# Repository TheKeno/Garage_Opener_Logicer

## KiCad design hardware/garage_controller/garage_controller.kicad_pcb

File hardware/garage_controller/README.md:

# Garage controller board (rev A)

A barebones board for `Garage_Opener_Logicer_R6`: an ATmega328P on a 16 MHz
crystal, powered from USB-C, with connectors for everything in the garage. The
chip is pinned out exactly like an Uno, so the sketch runs unchanged.

Open `garage_controller.kicad_pro` in KiCad 10. The schematic passes ERC with
no errors or warnings. The PCB has its outline, all footprints placed and every
pad on its net, and it matches the schematic exactly (DRC with schematic
parity). **It is not routed yet**: the only DRC items left are the 141
unrouted connections.

| File | |
|---|---|
| `garage_controller.kicad_sch` | schematic (A3, one sheet): each block drawn with wires, net labels only between blocks |
| `garage_controller.kicad_pcb` | 120 × 90 mm, 2 layers, placed, unrouted |
| `garage_controller.pdf`, `bom.csv`, `placement.png` | snapshots for reading without KiCad; re-export after edits |

## Connectors

| | Connector | Pins | Notes |
|---|---|---|---|
| J1 | USB-C (power only) | | 5.1k CC pull-downs, so any USB-C charger gives 5 V; 0.75 A polyfuse |
| J4 | LCD, JST-XH 4 | GND, 5V, SDA, SCL | standard PCF8574 backpack order; 4.7k pull-ups on board |
| J5 | Encoder, JST-XH 5 | CLK, DT, SW, +, GND | KY-040 order; SW is wired to D2 with the GUI button, so the knob's push works too |
| J6 | GUI button, JST-XH 2 | BTN, GND | to ground, D2 |
| J7 | Sonar, JST-XH 4 | VCC, TRIG, ECHO, GND | HC-SR04 order; series resistors for the long cable |
| J8 | Door microswitch, JST-XH 2 | SW, GND | 4.7k pull-up plus 1k/100 nF RC against noise on the long run |
| J9 | LDR, JST-XH 2 | 5V, A0 | 10k to ground on board, so more light reads higher |
| J10 | Opener, screw terminal 3 | NC, NO, COM | relay contacts: wire COM (pin 3) and NO (pin 2) across the opener's wall-button terminals |
| J11 | Park assist, JST-XH 5 | 5V, BUZ−, RED, GREEN, GND | 330 Ω on board for the LEDs; an active 5 V buzzer between 5V and BUZ− |
| J12 | ESP8266, 1×7 header | GND, 5V, TX, RX, DOOR_REQ, DOOR_STAT, CAR_STAT | 3.3 V signals; 5 V feeds the ESP board's own regulator |
| J2 | ISP, 2×3 | standard AVR ISP | for burning the bootloader |
| J3 | FTDI, 1×6 | GND, CTS, VCC, TX, RX, DTR | VCC is not connected, so power the board from USB-C while uploading |

## ESP8266 link

The ESP runs at 3.3 V and the ATmega at 5 V, so every line is shifted:

- **ESP TX → ATmega RX:** a BAT85 diode pulls a 10k-pulled-up line low. The idle
  high sits at about 3.6 V, comfortably above the ATmega's 3.0 V threshold.
- **ATmega → ESP** (RX, DOOR_STAT, CAR_STAT): 2.2k/3.3k dividers bring 5 V down
  to 3.0 V.
- **DOOR_REQ:** an NPN transistor plays the push button that R6 expects on D11
  (an active-low input with the internal pull-up). The ESP drives the pin
  **high** to press it. An unplugged ESP reads as "not pressed".

Two things in `esp/dooropener` disagree with R6 and need fixing on the ESP side:

- Its web page shows `DOOR: OPEN` when DOOR_STAT is high, but R6 drives
  `doorStatus` high when the door is **closed**.
- R6's comments describe the ESP as talking over the UART (OPEN / CLOSE /
  STATE …). The ESP sketch in the repo only uses the three pins.

## Building and flashing

1. Fit a **DIP-28 socket**. The footprint is sized for one, but the socket
   isn't in the BOM, so order it separately. Also order JST-XH housings and
   crimps for the cables.
2. Burn the bootloader once over J2. Use a USBasp, or a spare Uno running
   "Arduino as ISP". In the Arduino IDE, pick the **Arduino Uno** board and run
   *Burn Bootloader*. This also sets the fuses for the 16 MHz crystal.
3. Upload R6 over J3 with a 5 V FTDI adapter (DTR resets the chip
   automatically), or keep using the ISP header with *Upload Using Programmer*.
4. **Unplug the ESP for any programming.** It shares the UART with J3, and its
   DOOR_REQ transistor sits on D11, which is MOSI on the ISP header.

## Routing notes

- **Net classes:** a *Power* class (0.8 mm) covers +5V, GND, VBUS and the relay
  nets. Everything else is *Default* (0.3 mm).
- **Ground pour:** a GND zone covers the whole back layer but is left unfilled.
  Press `B` once the tracks are in.
- **Short traces:** keep the crystal (Y1, C6, C7) and the decoupling caps
  (C3, C4) short and close to U1.
- **Relay contacts:** J10's contacts only switch the opener's low-voltage
  button line, so normal clearances are fine. Don't use it for mains.

## Check before ordering

- **USB-C connector:** J1 is the one SMD part. It has six large pads and is
  easy to solder with an iron. Swap it for `Connector:USB_B` with
  `USB_B_OST_USB-B1HSxx_Horizontal` if you'd rather stay fully through-hole.
- **J10 orientation:** check in the 3D viewer that the wire entries face the
  board edge.
- **LDR resistor:** R12 (10k) has to match the resistor in your current build,
  or the light thresholds stored in EEPROM will be off.
- **Power budget:** about 0.6 A peak with the ESP, relay, LCD backlight and
  buzzer all on. Use a charger rated for at least 1 A.

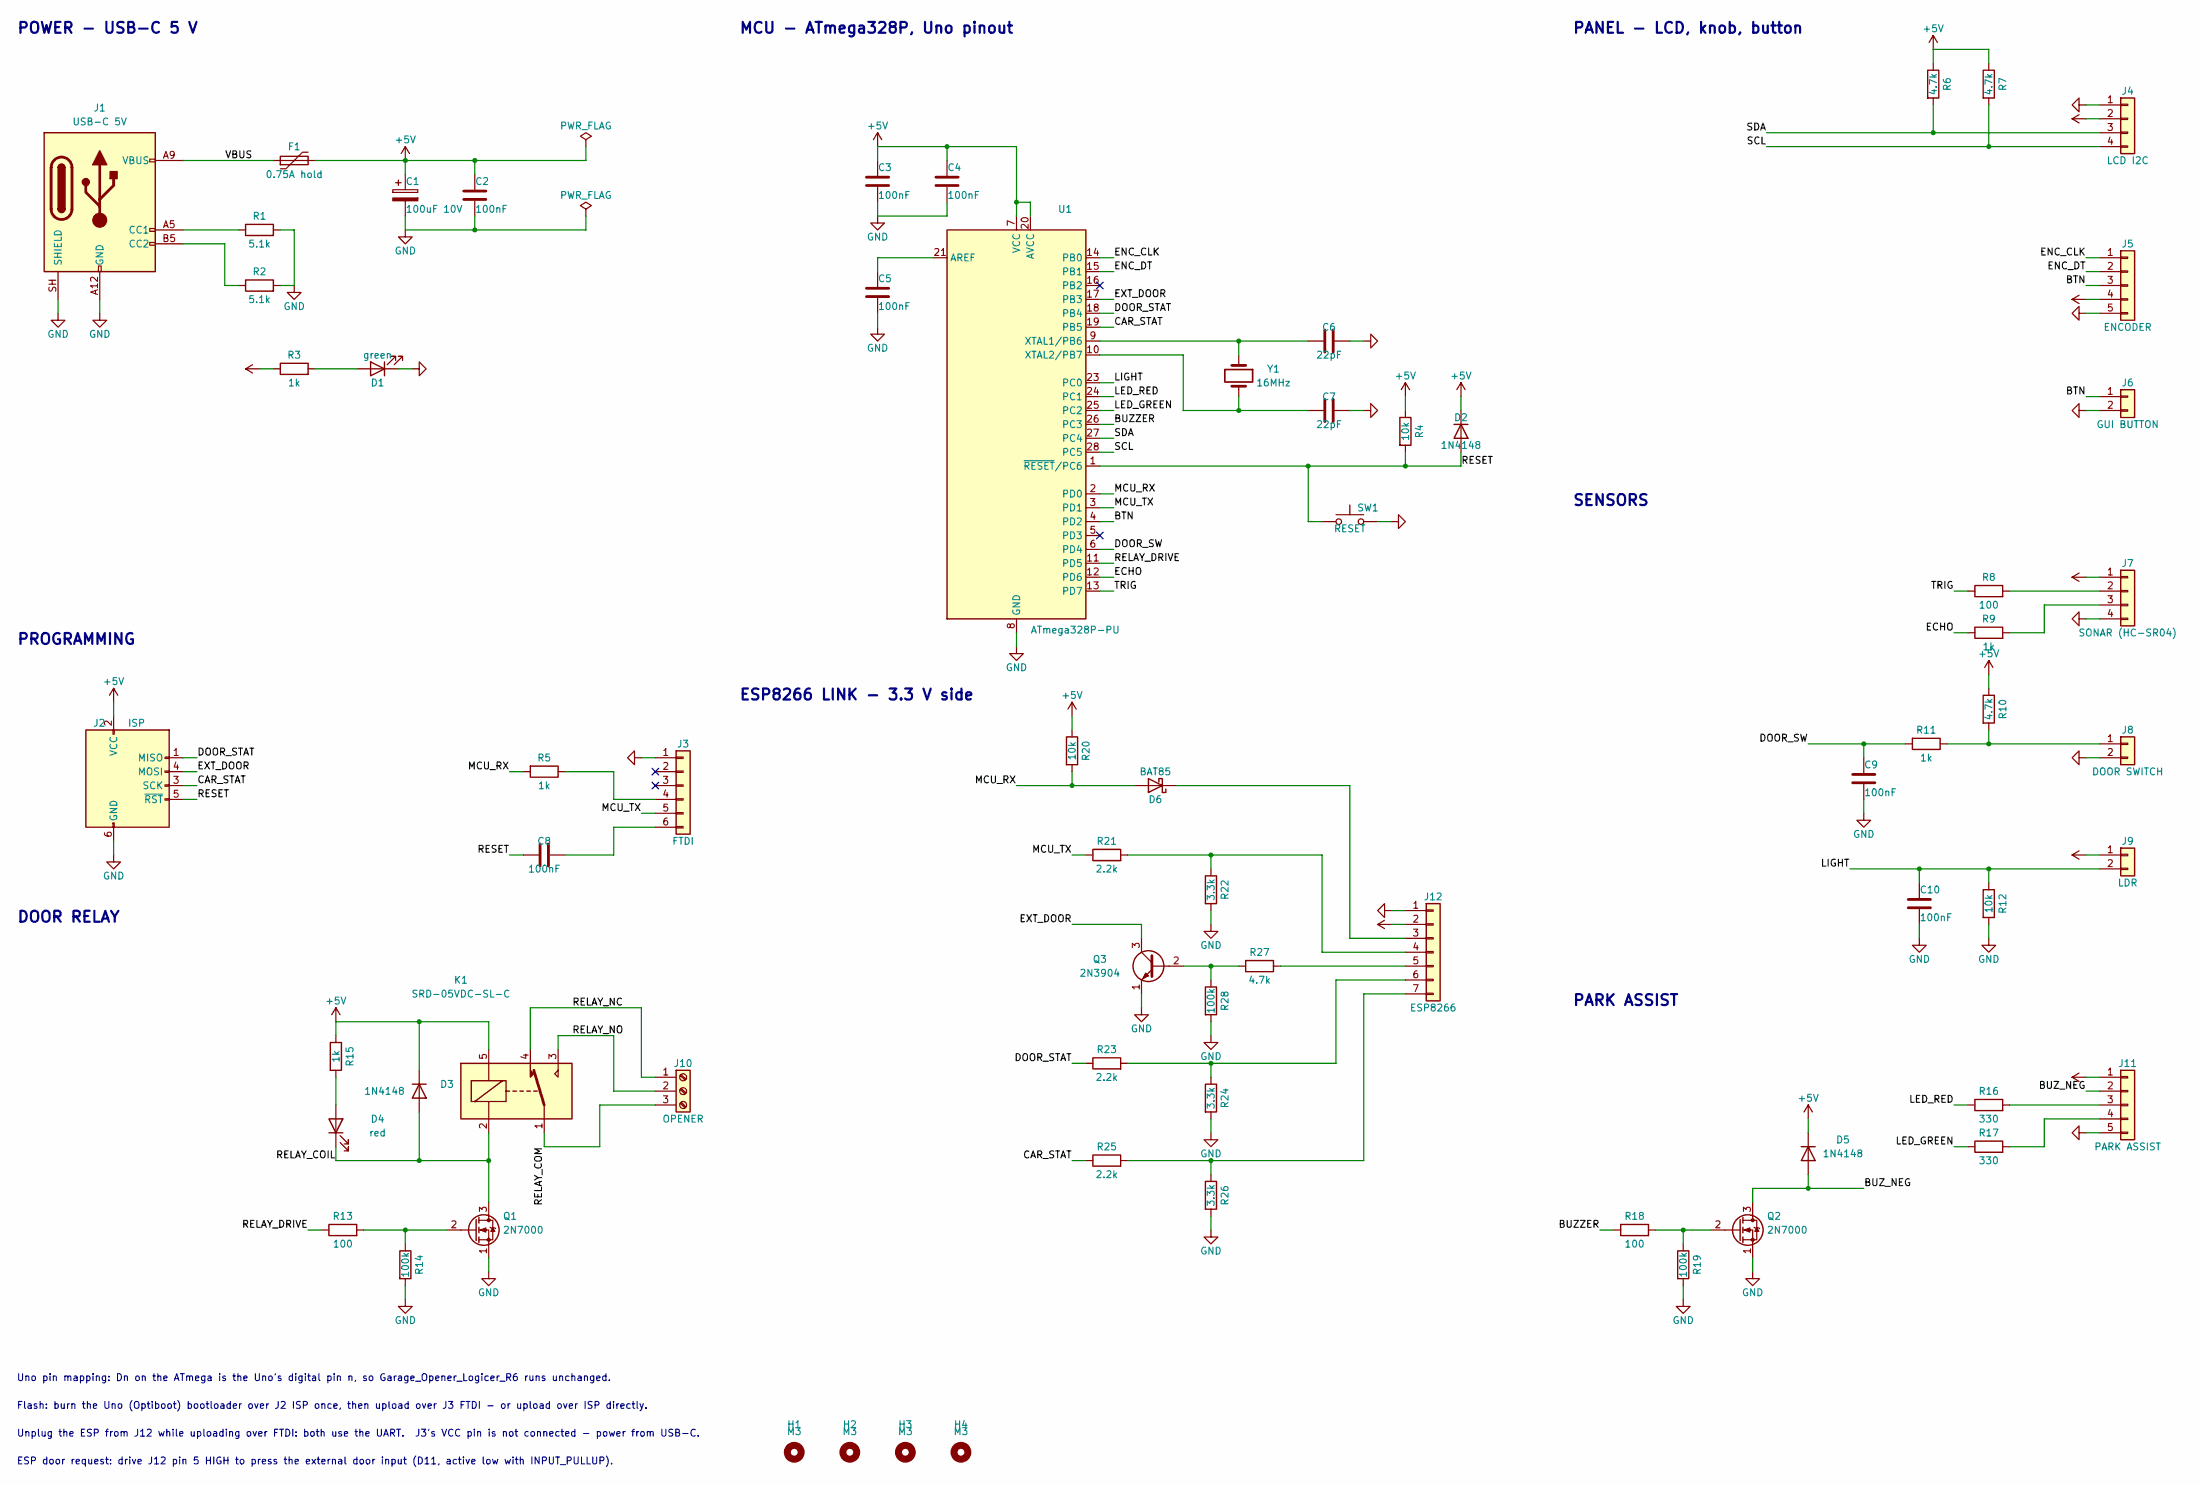
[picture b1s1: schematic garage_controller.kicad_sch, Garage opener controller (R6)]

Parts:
C1: 100uF 10V; CP_Radial_D6.3mm_P2.50mm
C2, C3, C4, C5, C8, C9, C10: 100nF; C_Disc_D5.0mm_W2.5mm_P5.00mm
C6, C7: 22pF; C_Disc_D5.0mm_W2.5mm_P5.00mm
D1: green; LED_D3.0mm
D2, D3, D5: 1N4148; D_DO-35_SOD27_P7.62mm_Horizontal
D4: red; LED_D3.0mm
D6: BAT85; D_DO-35_SOD27_P7.62mm_Horizontal
F1: 0.75A hold; Fuse_BelFuse_0ZRE0075FF_L11.5mm_W4.8mm
H1, H2, H3, H4: M3; MountingHole_3.2mm_M3
J1: USB-C 5V; USB_C_Receptacle_GCT_USB4125-xx-x_6P_TopMnt_Horizontal
J2: ISP; PinHeader_2x03_P2.54mm_Vertical
J3: FTDI; PinHeader_1x06_P2.54mm_Vertical
J4: LCD I2C; JST_XH_B4B-XH-A_1x04_P2.50mm_Vertical
J5: ENCODER; JST_XH_B5B-XH-A_1x05_P2.50mm_Vertical
J6: GUI BUTTON; JST_XH_B2B-XH-A_1x02_P2.50mm_Vertical
J7: SONAR (HC-SR04); JST_XH_B4B-XH-A_1x04_P2.50mm_Vertical
J8: DOOR SWITCH; JST_XH_B2B-XH-A_1x02_P2.50mm_Vertical
J9: LDR; JST_XH_B2B-XH-A_1x02_P2.50mm_Vertical
J10: OPENER; TerminalBlock_Phoenix_MKDS-1,5-3-5.08_1x03_P5.08mm_Horizont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
J11: PARK ASSIST; JST_XH_B5B-XH-A_1x05_P2.50mm_Vertical
J12: ESP8266; PinHeader_1x07_P2.54mm_Vertical
K1: SRD-05VDC-SL-C; Relay_SPDT_SANYOU_SRD_Series_Form_C
Q1, Q2: 2N7000; TO-92_Inline
Q3: 2N3904; TO-92_Inline
R1, R2: 5.1k; R_Axial_DIN0207_L6.3mm_D2.5mm_P10.16mm_Horizontal
R3, R5, R9, R11, R15: 1k; R_Axial_DIN0207_L6.3mm_D2.5mm_P10.16mm_Horizontal
R4, R12, R20: 10k; R_Axial_DIN0207_L6.3mm_D2.5mm_P10.16mm_Horizontal
R6, R7, R10, R27: 4.7k; R_Axial_DIN0207_L6.3mm_D2.5mm_P10.16mm_Horizontal
R8, R13, R18: 100; R_Axial_DIN0207_L6.3mm_D2.5mm_P10.16mm_Horizontal
R14, R19, R28: 100k; R_Axial_DIN0207_L6.3mm_D2.5mm_P10.16mm_Horizontal
R16, R17: 330; R_Axial_DIN0207_L6.3mm_D2.5mm_P10.16mm_Horizontal
R21, R23, R25: 2.2k; R_Axial_DIN0207_L6.3mm_D2.5mm_P10.16mm_Horizontal
R22, R24, R26: 3.3k; R_Axial_DIN0207_L6.3mm_D2.5mm_P10.16mm_Horizontal
SW1: RESET; SW_PUSH_6mm
U1: ATmega328P-PU; DIP-28_W7.62mm_Socket
Y1: 16MHz; Crystal_HC49-4H_Vertical

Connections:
+5V: C1.1, C2.1, C3.1, C4.1, D2.1 (K), D3.1 (K), D5.1 (K), F1.2, J2.2 (VCC), J4.2, J5.4, J7.1, J9.1, J11.1, J12.2, K1.5, R3.1, R4.1, R6.1, R7.1, R10.1, R15.1, R20.1, U1.7 (VCC), U1.20 (AVCC)
/BTN: J5.3, J6.1, U1.4 (PD2)
/BUZZER: R18.1, U1.26 (PC3)
/BUZ_NEG: D5.2 (A), J11.2, Q2.3 (D)
/CAR_STAT: J2.3 (SCK), R25.1, U1.19 (PB5)
/DOOR_STAT: J2.1 (MISO), R23.1, U1.18 (PB4)
/DOOR_SW: C9.1, R11.2, U1.6 (PD4)
/ECHO: R9.1, U1.12 (PD6)
/ENC_CLK: J5.1, U1.14 (PB0)
/ENC_DT: J5.2, U1.15 (PB1)
/EXT_DOOR: J2.4 (MOSI), Q3.3 (C), U1.17 (PB3)
/LED_GREEN: R17.1, U1.25 (PC2)
/LED_RED: R16.1, U1.24 (PC1)
/LIGHT: C10.1, J9.2, R12.1, U1.23 (PC0)
/MCU_RX: D6.2 (A), R5.2, R20.2, U1.2 (PD0)
/MCU_TX: J3.5, R21.1, U1.3 (PD1)
/RELAY_COIL: D3.2 (A), D4.1 (K), K1.2, Q1.3 (D)
/RELAY_COM: J10.3, K1.1
/RELAY_DRIVE: R13.1, U1.11 (PD5)
/RELAY_NC: J10.1, K1.4
/RELAY_NO: J10.2, K1.3
/RESET: C8.2, D2.2 (A), J2.5 (~RST), R4.2, SW1.1, U1.1 (~RESET/PC6)
/SCL: J4.4, R7.2, U1.28 (PC5)
/SDA: J4.3, R6.2, U1.27 (PC4)
/TRIG: R8.1, U1.13 (PD7)
/VBUS: F1.1, J1.A9 (VBUS), J1.B9 (VBUS)
GND: C1.2, C2.2, C3.2, C4.2, C5.2, C6.2, C7.2, C9.2, C10.2, D1.1 (K), J1.A12 (GND), J1.B12 (GND), J1.SH (SHIELD), J2.6 (GND), J3.1, J4.1, J5.5, J6.2, J7.4, J8.2, J11.5, J12.1, Q1.1 (S), Q2.1 (S), Q3.1 (E), R1.2, R2.2, R12.2, R14.2, R19.2, R22.2, R24.2, R26.2, R28.2, SW1.2, U1.8 (GND), U1.22 (GND)
unnamed: D1.2 (A), R3.2
unnamed: D4.2 (A), R15.2
unnamed: D6.1 (K), J12.3
unnamed: J1.A5 (CC1), R1.1
unnamed: J1.B5 (CC2), R2.1
unnamed: J3.4, R5.1
unnamed: C8.1, J3.6
unnamed: J7.2, R8.2
unnamed: J7.3, R9.2
unnamed: J8.1, R10.2, R11.1
unnamed: J11.3, R16.2
unnamed: J11.4, R17.2
unnamed: J12.4, R21.2, R22.1
unnamed: J12.5, R27.1
unnamed: J12.6, R23.2, R24.1
unnamed: J12.7, R25.2, R26.1
unnamed: Q1.2 (G), R13.2, R14.1
unnamed: Q2.2 (G), R18.2, R19.1
unnamed: Q3.2 (B), R27.2, R28.1
unnamed: C5.1, U1.21 (AREF)
unnamed: C6.1, U1.9 (XTAL1/PB6), Y1.1
unnamed: C7.1, U1.10 (XTAL2/PB7), Y1.2

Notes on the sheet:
MCU - ATmega328P, Uno pinout
Unplug the ESP from J12 while uploading over FTDI: both use the UART. J3's VCC pin is not connected - power from USB-C.
Uno pin mapping: Dn on the ATmega is the Uno's digital pin n, so Garage_Opener_Logicer_R6 runs unchanged.
SENSORS
PROGRAMMING
PANEL - LCD, knob, button
Flash: burn the Uno (Optiboot) bootloader over J2 ISP once, then upload over J3 FTDI - or upload over ISP directly.
ESP door request: drive J12 pin 5 HIGH to press the external door input (D11, active low with INPUT_PULLUP).
PARK ASSIST
DOOR RELAY
ESP8266 LINK - 3.3 V side
POWER - USB-C 5 V

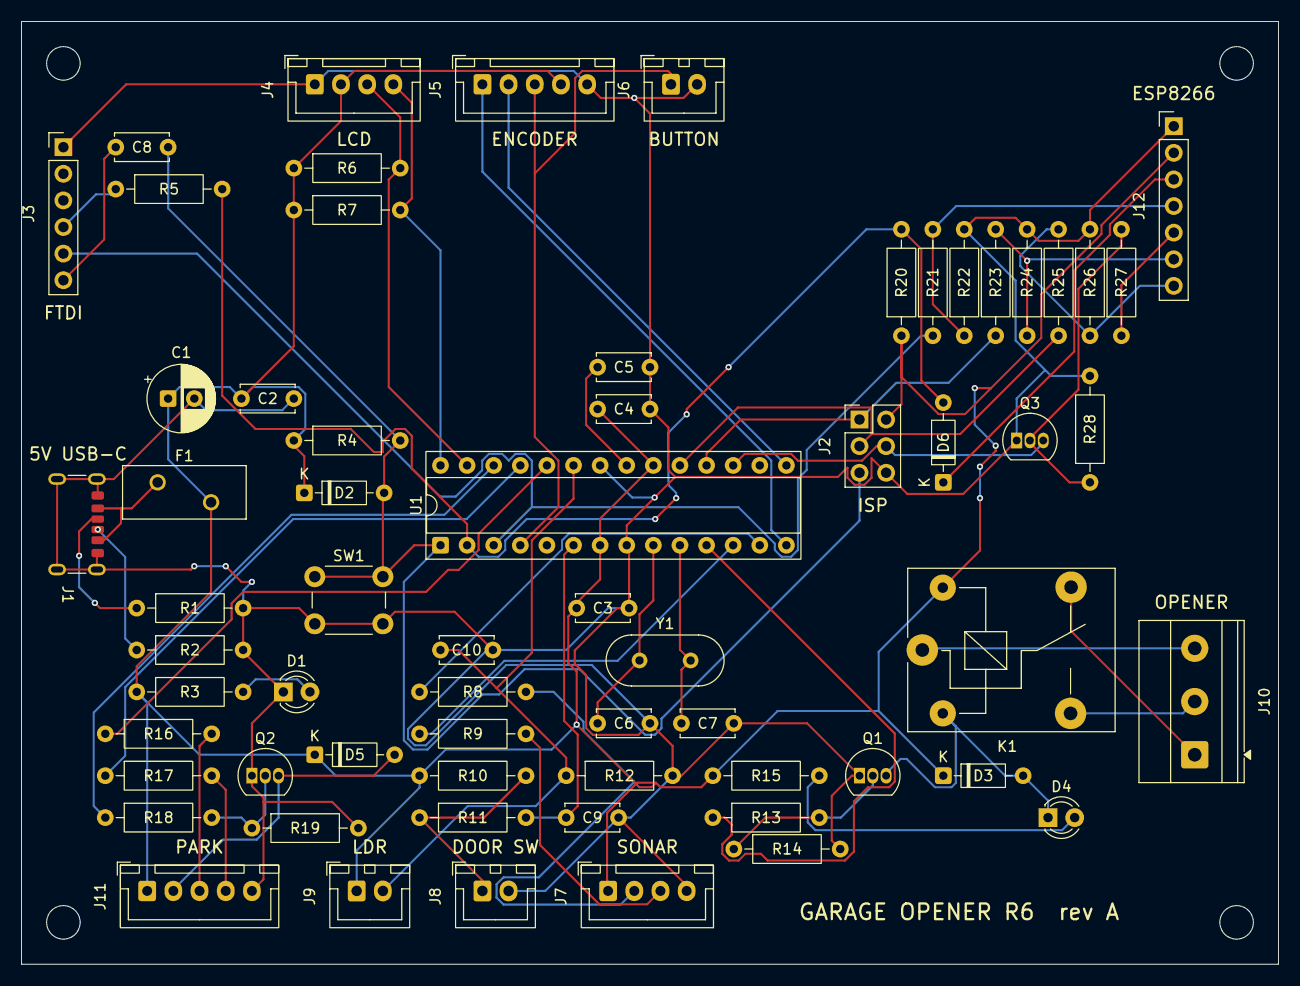
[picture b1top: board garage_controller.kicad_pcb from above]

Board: 2 copper layers, 120.0 x 90.0 mm, 68 parts (0 on the bottom side), 49 nets.

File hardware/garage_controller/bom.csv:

"Refs","Value","Footprint","Qty"
"C1","100uF 10V","Capacitor_THT:CP_Radial_D6.3mm_P2.50mm","1"
"C2,C3,C4,C5,C8,C9,C10","100nF","Capacitor_THT:C_Disc_D5.0mm_W2.5mm_P5.00mm","7"
"C6,C7","22pF","Capacitor_THT:C_Disc_D5.0mm_W2.5mm_P5.00mm","2"
"D1","green","LED_THT:LED_D3.0mm","1"
"D2,D3,D5","1N4148","Diode_THT:D_DO-35_SOD27_P7.62mm_Horizontal","3"
"D4","red","LED_THT:LED_D3.0mm","1"
"D6","BAT85","Diode_THT:D_DO-35_SOD27_P7.62mm_Horizontal","1"
"F1","0.75A hold","Fuse:Fuse_BelFuse_0ZRE0075FF_L11.5mm_W4.8mm","1"
"J1","USB-C 5V","Connector_USB:USB_C_Receptacle_GCT_USB4125-xx-x_6P_TopMnt_Horizontal","1"
"J2","ISP","Connector_PinHeader_2.54mm:PinHeader_2x03_P2.54mm_Vertical","1"
"J3","FTDI","Connector_PinHeader_2.54mm:PinHeader_1x06_P2.54mm_Vertical","1"
"J4","LCD I2C","Connector_JST:JST_XH_B4B-XH-A_1x04_P2.50mm_Vertical","1"
"J5","ENCODER","Connector_JST:JST_XH_B5B-XH-A_1x05_P2.50mm_Vertical","1"
"J6","GUI BUTTON","Connector_JST:JST_XH_B2B-XH-A_1x02_P2.50mm_Vertical","1"
"J7","SONAR (HC-SR04)","Connector_JST:JST_XH_B4B-XH-A_1x04_P2.50mm_Vertical","1"
"J8","DOOR SWITCH","Connector_JST:JST_XH_B2B-XH-A_1x02_P2.50mm_Vertical","1"
"J9","LDR","Connector_JST:JST_XH_B2B-XH-A_1x02_P2.50mm_Vertical","1"
"J10","OPENER","TerminalBlock_Phoenix:TerminalBlock_Phoenix_MKDS-1,5-3-5.08_1x03_P5.08mm_Horizontal","1"
"J11","PARK ASSIST","Connector_JST:JST_XH_B5B-XH-A_1x05_P2.50mm_Vertical","1"
"J12","ESP8266","Connector_PinHeader_2.54mm:PinHeader_1x07_P2.54mm_Vertical","1"
"K1","SRD-05VDC-SL-C","Relay_THT:Relay_SPDT_SANYOU_SRD_Series_Form_C","1"
"Q1,Q2","2N7000","Package_TO_SOT_THT:TO-92_Inline","2"
"Q3","2N3904","Package_TO_SOT_THT:TO-92_Inline","1"
"R1,R2","5.1k","Resistor_THT:R_Axial_DIN0207_L6.3mm_D2.5mm_P10.16mm_Horizontal","2"
"R3,R5,R9,R11,R15","1k","Resistor_THT:R_Axial_DIN0207_L6.3mm_D2.5mm_P10.16mm_Horizontal","5"
"R4,R12,R20","10k","Resistor_THT:R_Axial_DIN0207_L6.3mm_D2.5mm_P10.16mm_Horizontal","3"
"R6,R7,R10,R27","4.7k","Resistor_THT:R_Axial_DIN0207_L6.3mm_D2.5mm_P10.16mm_Horizontal","4"
"R8,R13,R18","100","Resistor_THT:R_Axial_DIN0207_L6.3mm_D2.5mm_P10.16mm_Horizontal","3"
"R14,R19,R28","100k","Resistor_THT:R_Axial_DIN0207_L6.3mm_D2.5mm_P10.16mm_Horizontal","3"
"R16,R17","330","Resistor_THT:R_Axial_DIN0207_L6.3mm_D2.5mm_P10.16mm_Horizontal","2"
"R21,R23,R25","2.2k","Resistor_THT:R_Axial_DIN0207_L6.3mm_D2.5mm_P10.16mm_Horizontal","3"
"R22,R24,R26","3.3k","Resistor_THT:R_Axial_DIN0207_L6.3mm_D2.5mm_P10.16mm_Horizontal","3"
"SW1","RESET","Button_Switch_THT:SW_PUSH_6mm","1"
"U1","ATmega328P-PU","Package_DIP:DIP-28_W7.62mm_Socket","1"
"Y1","16MHz","Crystal:Crystal_HC49-4H_Vertical","1"

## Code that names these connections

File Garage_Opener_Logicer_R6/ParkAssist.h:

#ifndef PARK_ASSIST_H
#define PARK_ASSIST_H

#include "Arduino.h"

class ParkAssist {
public:
	ParkAssist(int led_red_pin, int led_green_pin, int buzzer_pin,
	           unsigned long min_beep_interval, unsigned long max_beep_interval,
	           unsigned long beep_on_duration, unsigned long hold_time);

	void begin();
	// Call once on entering STATE_PARKING: red on, buzzer/timers cleared.
	void reset();
	// Call once on leaving STATE_PARKING: LEDs + buzzer off.
	void off();

	// Call every loop while in STATE_PARKING. Drives the LED/buzzer from the
	// current distance reading. Returns true once the near-distance goal has
	// been held continuously for hold_time.
	bool update(int distance, int16_t far_distance, int16_t near_distance);

private:
	int led_red_pin;
	int led_green_pin;
	int buzzer_pin;

	unsigned long min_beep_interval;
	unsigned long max_beep_interval;
	unsigned long beep_on_duration;
	unsigned long hold_time;

	bool buzzer_on = false;
	unsigned long last_beep_toggle = 0;
	unsigned long parked_since = 0; // 0 = not currently holding at the goal
};

#endif

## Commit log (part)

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2025-10-25 asdasd
2025-10-25 Fixes light levels
2025-10-25 Add distance and light level outputs to display in idle state
2025-10-25 Added labels to LCD print
2025-10-25 tabs instead of spaces
2025-10-25 Fixed button usage
2025-10-26 Added and changed PINs
2025-10-26 fixade pinfel
2025-10-26 Fixed pointer error
2025-10-26 pin changes
2025-10-26 Moved distanceSensor to own files
2025-10-26 First try at light pulse sensor
2025-10-26 Use light pulse sensor
2025-10-26 Added config state
2025-10-26 Fixing button issues
2025-10-26 changed board to arduino. Does not compile with that board
2025-10-26 Replaced printf on lcd with snprintf+print
2025-10-26 make use of saved values
2025-10-26 more
2025-10-26 500ms
2025-10-26 Fixed config values under 0
2025-10-27 Added average light level sampling to light pulse sensor
2025-10-27 fixes and changes
2025-10-28 Moved constans and pin setup to config.h
2025-10-29 Added FPS counter
2025-10-29 Add fps to serial monitor
2025-10-29 unfuck
2025-10-29 Made distance sensor only run once per second
2025-11-02 added pin configs
2025-11-02 Fixed name
2025-11-02 Add reporting code, changed min/max config threshold
2025-11-02 Chngeds saker
2025-11-02 Added garage door web interface
2025-11-02 settings tweaked
2025-11-04 config change
2026-03-29 Timings and defaults
